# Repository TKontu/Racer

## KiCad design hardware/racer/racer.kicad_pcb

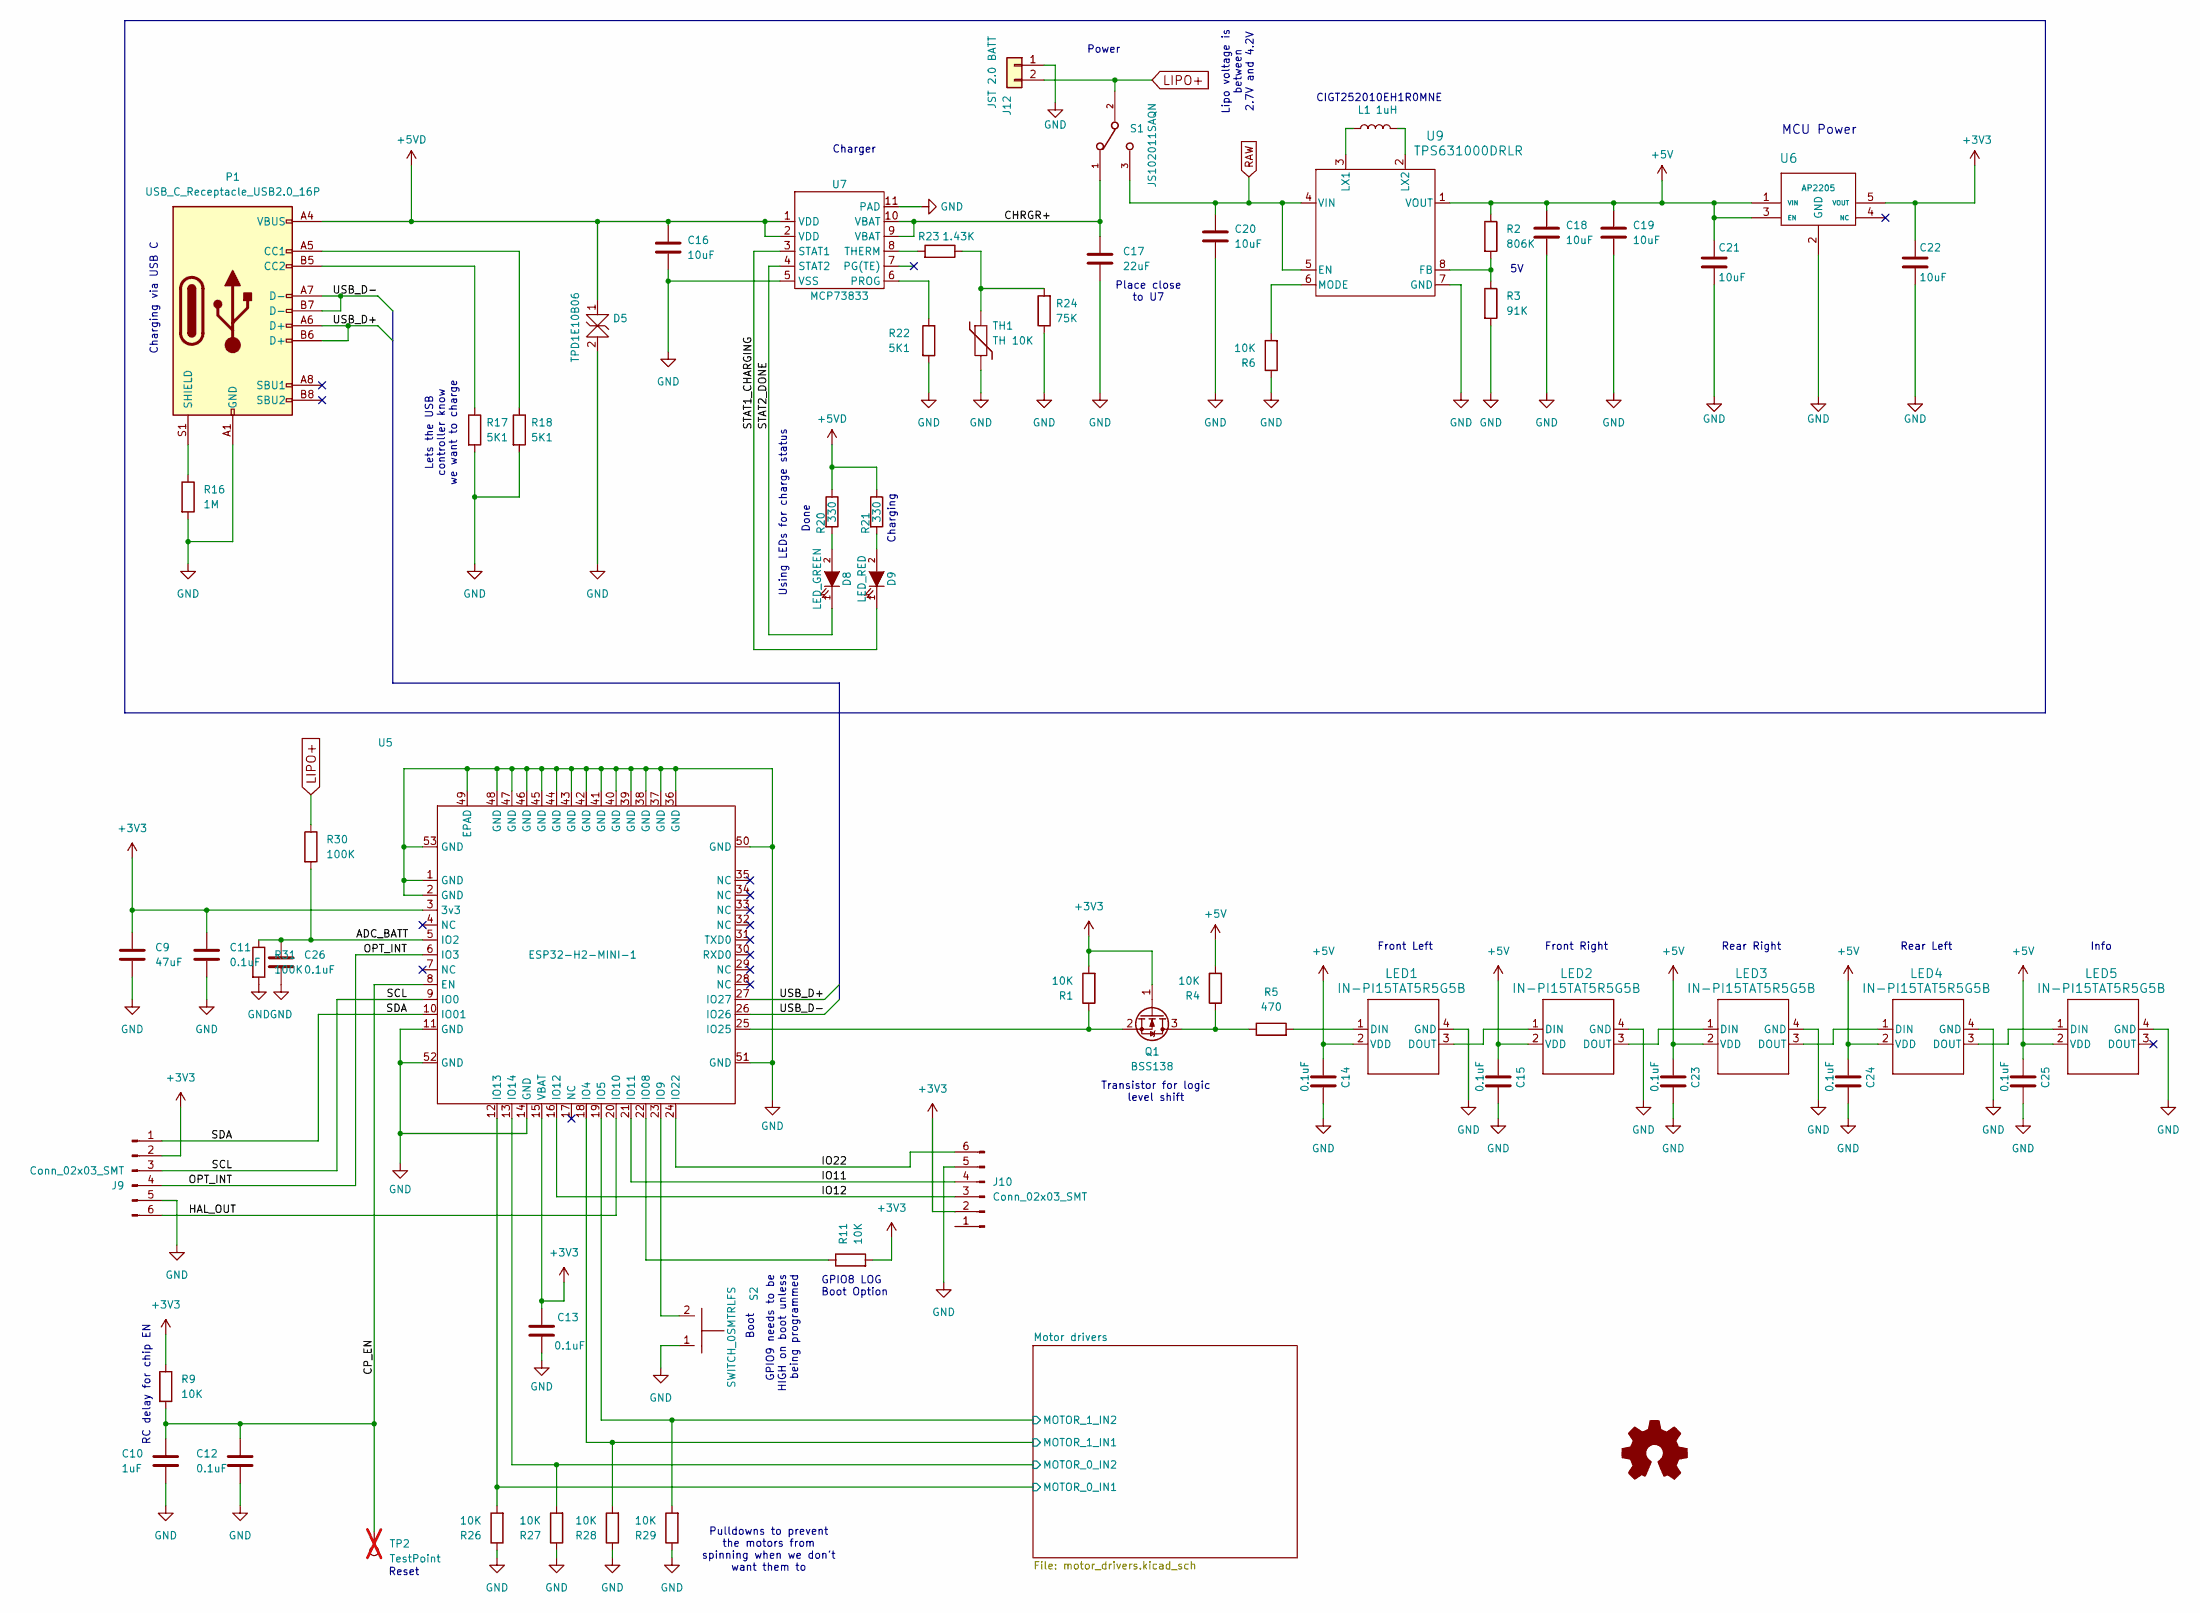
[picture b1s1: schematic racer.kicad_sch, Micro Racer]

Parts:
C9: 47uF; C_0603_1608Metric; MPN GRM188R60J476ME15D; LCSC C140782
C10: 1uF; C_0603_1608Metric; MPN CC0603KRX5R8BB105; LCSC C14664
C11, C12, C13, C14, C15, C23, C24, C25, C26: 0.1uF; C_0603_1608Metric; MPN CC0603KRX7R7BB104; LCSC C108079
C16, C18, C19, C20, C21, C22: 10uF; C_0603_1608Metric; MPN GRM188R61A106ME69D; LCSC C90053
C17: 22uF; C_0603_1608Metric; MPN GRM188R60J226MEA0J; LCSC C426040
D5: TPD1E10B06; D_SOD-523; MPN TPD1E10B06DYAR; LCSC C3712135
D8: LED_GREEN; C_0603_1608Metric; MPN 19-217/GHC-YR1S2/3T; LCSC C72043
D9: LED_RED; C_0603_1608Metric; MPN KT-0603R; LCSC C2286
J9, J10: Conn_02x03_SMT; PinHeader_2x03_P1.27mm_Vertical_SMD; MPN GRPB032VWQS-RC; LCSC C5646308
J12: JST 2.0 BATT; JST_PH_B2B-PH-K_1x02_P2.00mm_Vertical; MPN B2B-PH-K-S(LF)(SN); LCSC C131337
L1: 1uH; RES_CIGT252010; MPN CIGT252010LM1R0MNE; LCSC C307632
LED1, LED2, LED3, LED4, LED5: IN-PI15TAT5R5G5B; IN-PI15_INL; MPN IN-PI15TAT5R5G5B; LCSC C7429437
P1: USB_C_Receptacle_USB2.0_16P; GCT_USB4105-GF-A; MPN USB4105-GF-A; LCSC C3020560
Q1: BSS138; SOT-23; MPN BSS138; LCSC C52895
R1, R4, R6, R9, R11, R26, R27, R28, R29: 10K; R_0603_1608Metric; MPN WR06X103JTL; LCSC C384294
R2: 806K; R_0603_1608Metric; MPN RC0603FR-07806KL; LCSC C185311
R3: 91K; R_0603_1608Metric; MPN AR0603FR-0791KL; LCSC C855484
R5: 470; R_0603_1608Metric; MPN 0603WAF4700T5E; LCSC C23179
R16: 1M; R_0603_1608Metric; MPN RMCF0603FT1M00; LCSC C237111
R17, R18, R22: 5K1; R_0603_1608Metric; MPN RC0603FR-075K1L; LCSC C105580
R20, R21: 330; R_0603_1608Metric; MPN RC0603JR-07330RL; LCSC C105879
R23: 1.43K; R_0603_1608Metric; MPN RT0603BRE071K43L; LCSC C861730
R24: 75K; R_0603_1608Metric; MPN ERJ-PB3B7502V; LCSC C413688
R30, R31: 100K; R_0603_1608Metric; MPN WR06X1003FTL; LCSC C132374
S1: JS102011SAQN; SW_JS102011SAQN; MPN JS102011SAQN; LCSC C221660
S2: SWITCH_0SMTRLFS; MPN RKB2SJK250SMTRLFS; LCSC C2927789
TH1: TH 10K; R_0603_1608Metric; MPN NTCG163JF103HT1; LCSC C531304
TP2: TestPoint; TestPoint_Pad_1.5x1.5mm; not fitted
U5: ESP32-H2-MINI-1; MODULE_ESP32-H2-MINI-1-H2; MPN ESP32-H2-MINI-1-N4; LCSC C18203134
U6: AP2205; AP2204; MPN AP2205-33W5-7; LCSC C3750488
U7: MCP73833; SON50P300X300X100-11N; MPN MCP73833T-AMI/MF; LCSC C340160
U9: TPS631000DRLR; TPS631000DRLR_TEX; MPN TPS631000DRLR; LCSC C5219190

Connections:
+3V3: C9.1, C11.1, C13.1, C22.1, J9.2, J10.2, Q1.1 (G), R1.2, R9.1, R11.2, U5.3 (3v3), U5.15 (VBAT), U6.5 (VOUT)
+5V: C14.1, C15.1, C18.1, C19.1, C21.1, C23.1, C24.1, C25.1, LED1.2 (VDD), LED2.2 (VDD), LED3.2 (VDD), LED4.2 (VDD), LED5.2 (VDD), R2.1, R4.2, U6.1 (VIN), U6.3 (EN), U9.1 (VOUT)
+5VD: C16.1, D5.1, P1.A4 (VBUS), P1.A9 (VBUS), P1.B4 (VBUS), P1.B9 (VBUS), R20.1, R21.1, U7.1 (VDD), U7.2 (VDD)
/ADC_BATT: C26.1, R30.2, R31.1, U5.5 (IO2)
/CHRGR+: C17.1, S1.1, U7.9 (VBAT), U7.10 (VBAT)
/CP_EN: C10.1, C12.1, R9.2, TP2.1, U5.8 (EN)
/HAL_OUT: J9.6, U5.20 (IO10)
/IO11: J10.4, U5.21 (IO11)
/IO12: J10.3, U5.16 (IO12)
/IO22: J10.6, U5.24 (IO22)
/OPT_INT: J9.4, U5.6 (IO3)
/SCL: J9.3, U5.9 (IO0)
/SDA: J9.1, U5.10 (IO01)
/STAT1_CHARGING: D9.1 (K), U7.3 (STAT1)
/STAT2_DONE: D8.1 (K), U7.4 (STAT2)
/USB_D+: P1.A6 (D+), P1.B6 (D+), U5.27 (IO27)
/USB_D-: P1.A7 (D-), P1.B7 (D-), U5.26 (IO26)
GND: C9.2, C10.2, C11.2, C12.2, C13.2, C14.2, C15.2, C16.2, C17.2, C18.2, C19.2, C20.2, C21.2, C22.2, C23.2, C24.2, C25.2, C26.2, D5.2, J9.5, J10.5, J12.1, LED1.4 (GND), LED2.4 (GND), LED3.4 (GND), LED4.4 (GND), LED5.4 (GND), P1.A1 (GND), P1.A12 (GND), P1.B1 (GND), P1.B12 (GND), R3.2, R6.1, R16.2, R17.2, R18.2, R22.2, R24.1, R26.1, R27.1, R28.1, R29.1, R31.2, S2.1, TH1.2, U5.1 (GND), U5.2 (GND), U5.11 (GND), U5.14 (GND), U5.36 (GND), U5.37 (GND), U5.38 (GND), U5.39 (GND), U5.40 (GND), U5.41 (GND), U5.42 (GND), U5.43 (GND), U5.44 (GND), U5.45 (GND), U5.46 (GND), U5.47 (GND), U5.48 (GND), U5.49 (EPAD), U5.50 (GND), U5.51 (GND), U5.52 (GND), U5.53 (GND), U6.2 (GND), U7.5 (VSS), U7.11 (PAD), U9.7 (GND); also elsewhere on the board
LIPO+: J12.2, R30.1, S1.2
MOTOR_0_IN1: R26.2, U5.12 (IO13); also elsewhere on the board
MOTOR_0_IN2: R27.2, U5.13 (IO14); also elsewhere on the board
MOTOR_1_IN1: R28.2, U5.18 (IO4); also elsewhere on the board
MOTOR_1_IN2: R29.2, U5.19 (IO5); also elsewhere on the board
unnamed: D8.2 (A), R20.2
unnamed: D9.2 (A), R21.2
unnamed: LED1.1 (DIN), R5.2
unnamed: LED1.3 (DOUT), LED2.1 (DIN)
unnamed: LED2.3 (DOUT), LED3.1 (DIN)
unnamed: LED3.3 (DOUT), LED4.1 (DIN)
unnamed: LED4.3 (DOUT), LED5.1 (DIN)
unnamed: P1.A5 (CC1), R18.1
unnamed: P1.B5 (CC2), R17.1
unnamed: P1.S1 (SHIELD), R16.1
unnamed: Q1.3 (D), R4.1, R5.1
unnamed: Q1.2 (S), R1.1, U5.25 (IO25)
unnamed: R23.1, R24.2, TH1.1
unnamed: R11.1, U5.22 (IO08)
unnamed: S2.2, U5.23 (IO9)
unnamed: R22.1, U7.6 (PROG)
unnamed: R23.2, U7.8 (THERM)
unnamed: R2.2, R3.1, U9.8 (FB)
unnamed: L1.1, U9.3 (LX1)
unnamed: L1.2, U9.2 (LX2)
unnamed: R6.2, U9.6 (MODE)
RAW: C20.1, S1.3, U9.4 (VIN), U9.5 (EN); also elsewhere on the board

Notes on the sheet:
Lipo voltage is between 2.7V and 4.2V
Charging via USB C
Using LEDs for charge status
RC delay for chip EN
Lets the USB controller know we want to charge
Front Right
Power
Rear Right
Reset
GPIO9 needs to be HIGH on boot unless being programmed
Pulldowns to prevent the motors from spinning when we don't want them to
Charger
GPIO8 LOG Boot Option
Charging
Done
Info
MCU Power
Front Left
CIGT252010EH1R0MNE
Rear Left
Place close to U7
Boot
Transistor for logic level shift

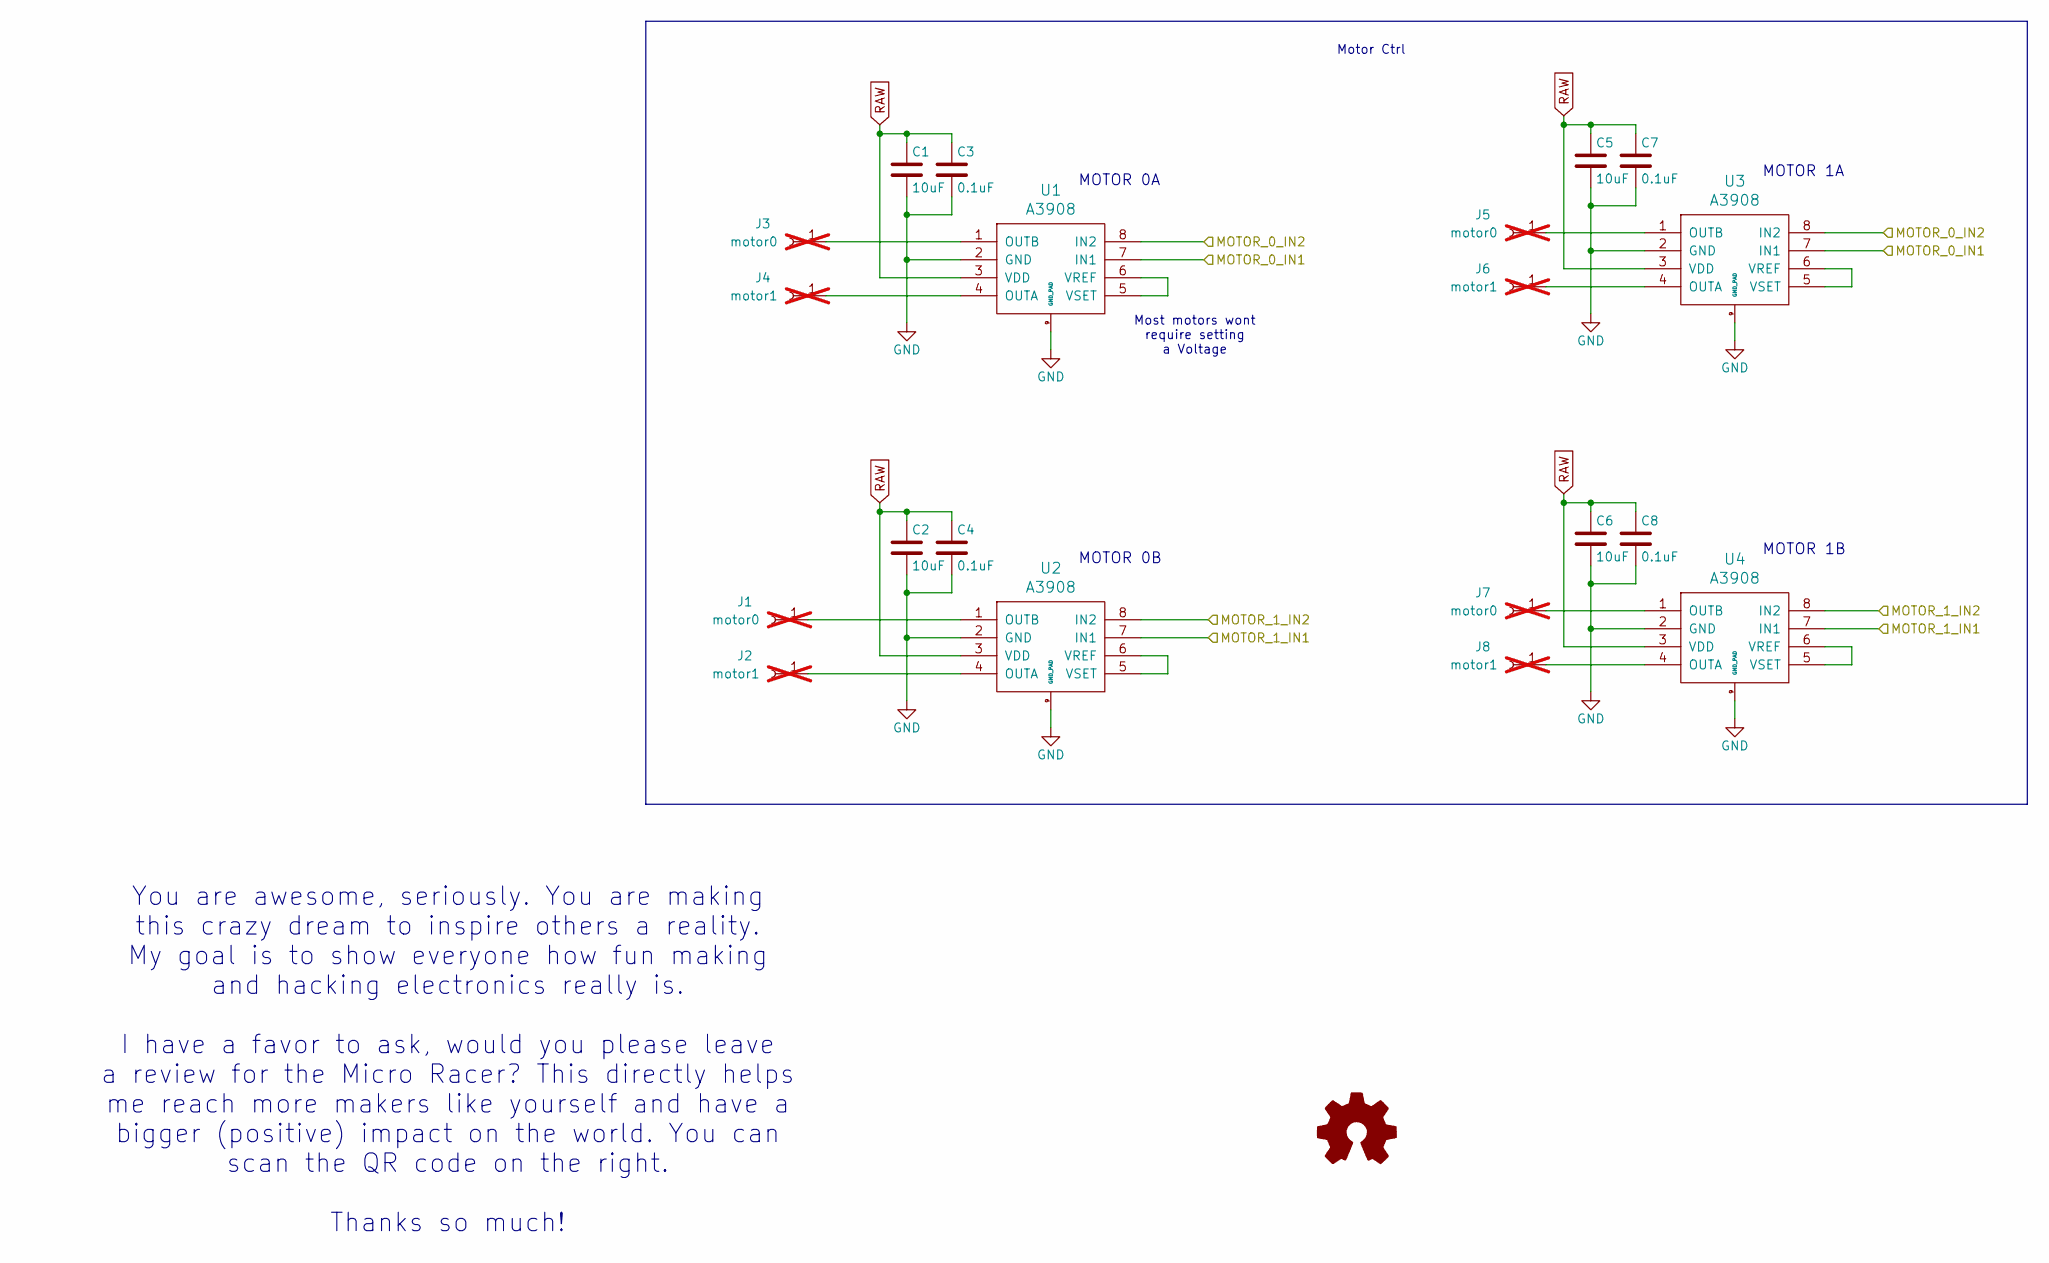
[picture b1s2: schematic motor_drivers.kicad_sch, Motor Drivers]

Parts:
C1, C2, C5, C6: 10uF; C_0603_1608Metric; MPN GRM188R61A106ME69D; LCSC C90053
C3, C4, C7, C8: 0.1uF; C_0603_1608Metric; MPN CC0603KRX7R7BB104; LCSC C108079
J1, J3, J5, J7: motor0; TestPoint_Pad_2.0x2.0mm; not fitted
J2, J4, J6, J8: motor1; TestPoint_Pad_2.0x2.0mm; not fitted
U1, U2, U3, U4: A3908; MPN A3908EEETR-T; LCSC C459250

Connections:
GND: C1.2, C2.2, C3.2, C4.2, C5.2, C6.2, C7.2, C8.2, U1.2 (GND), U1.9 (GND_PAD), U2.2 (GND), U2.9 (GND_PAD), U3.2 (GND), U3.9 (GND_PAD), U4.2 (GND), U4.9 (GND_PAD); also elsewhere on the board
MOTOR_0_IN1: U1.7 (IN1), U3.7 (IN1); also elsewhere on the board
MOTOR_0_IN2: U1.8 (IN2), U3.8 (IN2); also elsewhere on the board
MOTOR_1_IN1: U2.7 (IN1), U4.7 (IN1); also elsewhere on the board
MOTOR_1_IN2: U2.8 (IN2), U4.8 (IN2); also elsewhere on the board
unnamed: J1.1, U2.1 (OUTB)
unnamed: J2.1, U2.4 (OUTA)
unnamed: J3.1, U1.1 (OUTB)
unnamed: J4.1, U1.4 (OUTA)
unnamed: J5.1, U3.1 (OUTB)
unnamed: J6.1, U3.4 (OUTA)
unnamed: J7.1, U4.1 (OUTB)
unnamed: J8.1, U4.4 (OUTA)
unnamed: U1.5 (VSET), U1.6 (VREF)
unnamed: U2.5 (VSET), U2.6 (VREF)
unnamed: U3.5 (VSET), U3.6 (VREF)
unnamed: U4.5 (VSET), U4.6 (VREF)
RAW: C1.1, C2.1, C3.1, C4.1, C5.1, C6.1, C7.1, C8.1, U1.3 (VDD), U2.3 (VDD), U3.3 (VDD), U4.3 (VDD); also elsewhere on the board

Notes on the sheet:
Most motors wont require setting a Voltage
You are awesome, seriously. You are making this crazy dream to inspire others a reality. My goal is to show everyone how fun making and hacking electronics really is. I have a favor to ask, would you please leave a review for the Micro Racer? This directly helps me reach more makers like yourself a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
MOTOR 1B
MOTOR 0A
Motor Ctrl
MOTOR 1A
MOTOR 0B

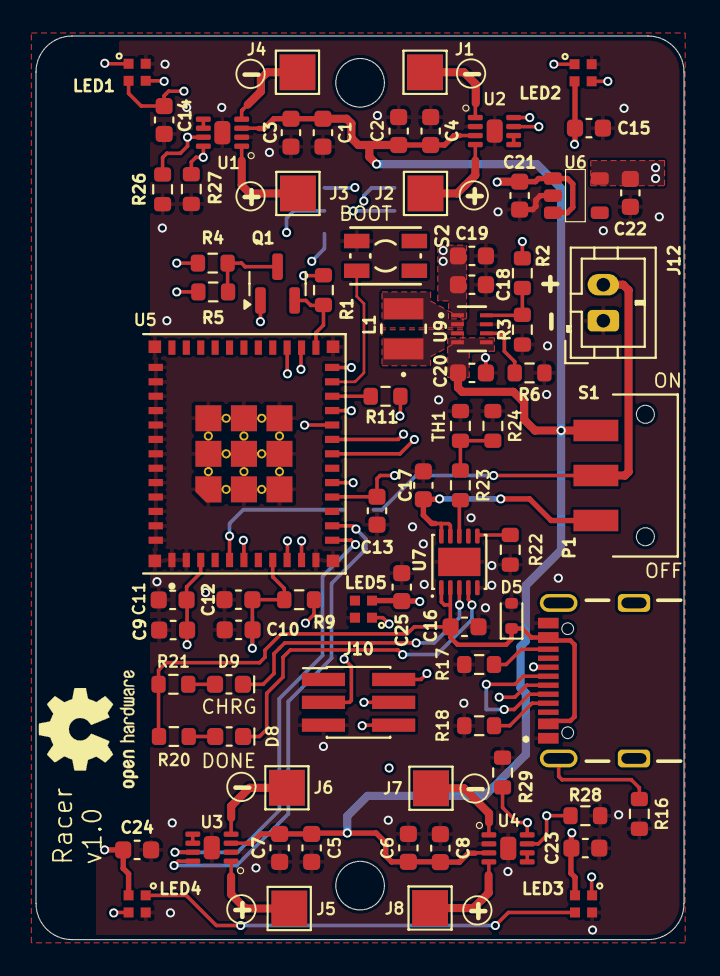
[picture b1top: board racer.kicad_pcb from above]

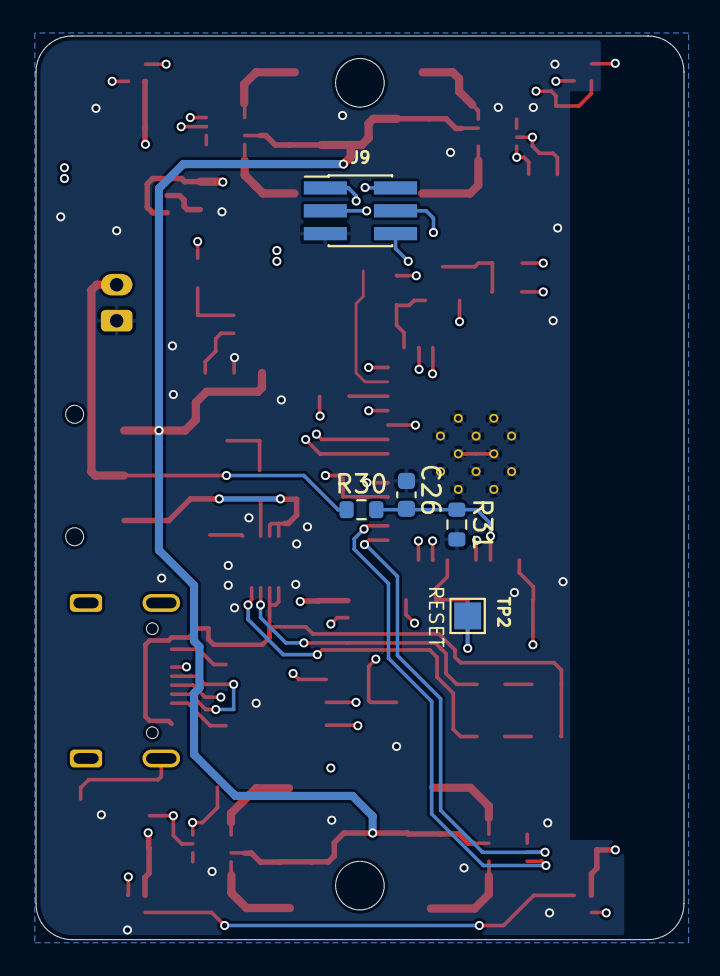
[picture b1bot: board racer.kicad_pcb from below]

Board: 4 copper layers, 36.0 x 50.2 mm, 82 parts (5 on the bottom side), 57 nets.

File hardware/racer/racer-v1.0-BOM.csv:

Designator,Quantity,Manufacturer Part Number,Package/Footprint,Description
U9,1,TPS631000DRLR,TPS631000DRLR_TEX,TPS631000DRLR
"R6,R26,R28,R29,R9,R1,R27,R11,R4",9,WR06X103 JTL,R_0603_1608Metric,10K
"C2,C16,C20,C18,C5,C6,C19,C1,C22,C21",10,GRM188R61A106ME69D,C_0603_1608Metric,10uF
S2,1,RKB2SJK250SMTR LFS,SWITCH_0SMTRLFS,SWITCH_0SMTRLFS
"C7,C12,C13,C24,C15,C3,C8,C14,C4,C23,C11,C25,C26",13,CC0603KRX7R7BB104,C_0603_1608Metric,0.1uF
R2,1,RC0603FR-07806KL,R_0603_1608Metric,806K
U6,1,AP2205-33W5-7,AP2204,AP2205
R23,1,RT0603BRE071K43L,R_0603_1608Metric,1.43K
"J9,J10",2,GRPB032VWQS-RC,PinHeader_2x03_P1.27mm_Vertical_SMD,Conn_02x03_SMT
Q1,1,BSS138,SOT-23,BSS138
D9,1,150060RS75000,C_0603_1608Metric,LED_RED
"R17,R22,R18",3,RC0603FR-075K1L,R_0603_1608Metric,5K1
"LED1,LED3,LED5,LED4,LED2",5,IN-PI15TAT5R5G5B,IN-PI15_INL,IN-PI15TAT5R5G5B
D8,1,150060GS75000,C_0603_1608Metric,LED_GREEN
"U4,U1,U2,U3",4,A3908EEETR-T,A3908,A3908
J12,1,B2B-PH-K-S,JST_PH_B2B-PH-K_1x02_P2.00mm_Vertical,JST 2.0 BATT
P1,1,USB4105-GF-A,GCT_USB4105-GF-A,USB_C_Receptacle_USB2.0_16P
TH1,1,NTCG163JF103HT1,R_0603_1608Metric,TH 10K
U5,1,ESP32-H2-MINI-1,MODULE_ESP32-H2-MINI-1-H2,ESP32-H2-MINI-1
R3,1,AR0603FR-0791KL,R_0603_1608Metric,91K
R5,1,ESR03EZPF4700,R_0603_1608Metric,470
L1,1,CIGT252010EH1R0MNE,RES_CIGT252010,1uH
C10,1,CC0603KRX5R8BB105,C_0603_1608Metric,1uF
"R21,R20",2,RC0603JR-07330RL,R_0603_1608Metric,330
D5,1,TPD1E10B06DYAR,D_SOD-523,TPD1E10B06
S1,1,JS102011SAQN,SW_JS102011SAQN,JS102011SAQN
R24,1,ERJ-PB3B7502V,R_0603_1608Metric,75K
U7,1,MCP73833T-AMI/MF,SON50P300X300X100-11N,MCP73833
C17,1,GRM188R60J226MEA0J,C_0603_1608Metric,22uF
R16,1,RMCF0603FT1M00,R_0603_1608Metric,1M
C9,1,GRM188R60J476ME15D,C_0603_1608Metric,47uF
"R30,R31",2,WR06X1003FTL,R_0603_1608Metric,100K

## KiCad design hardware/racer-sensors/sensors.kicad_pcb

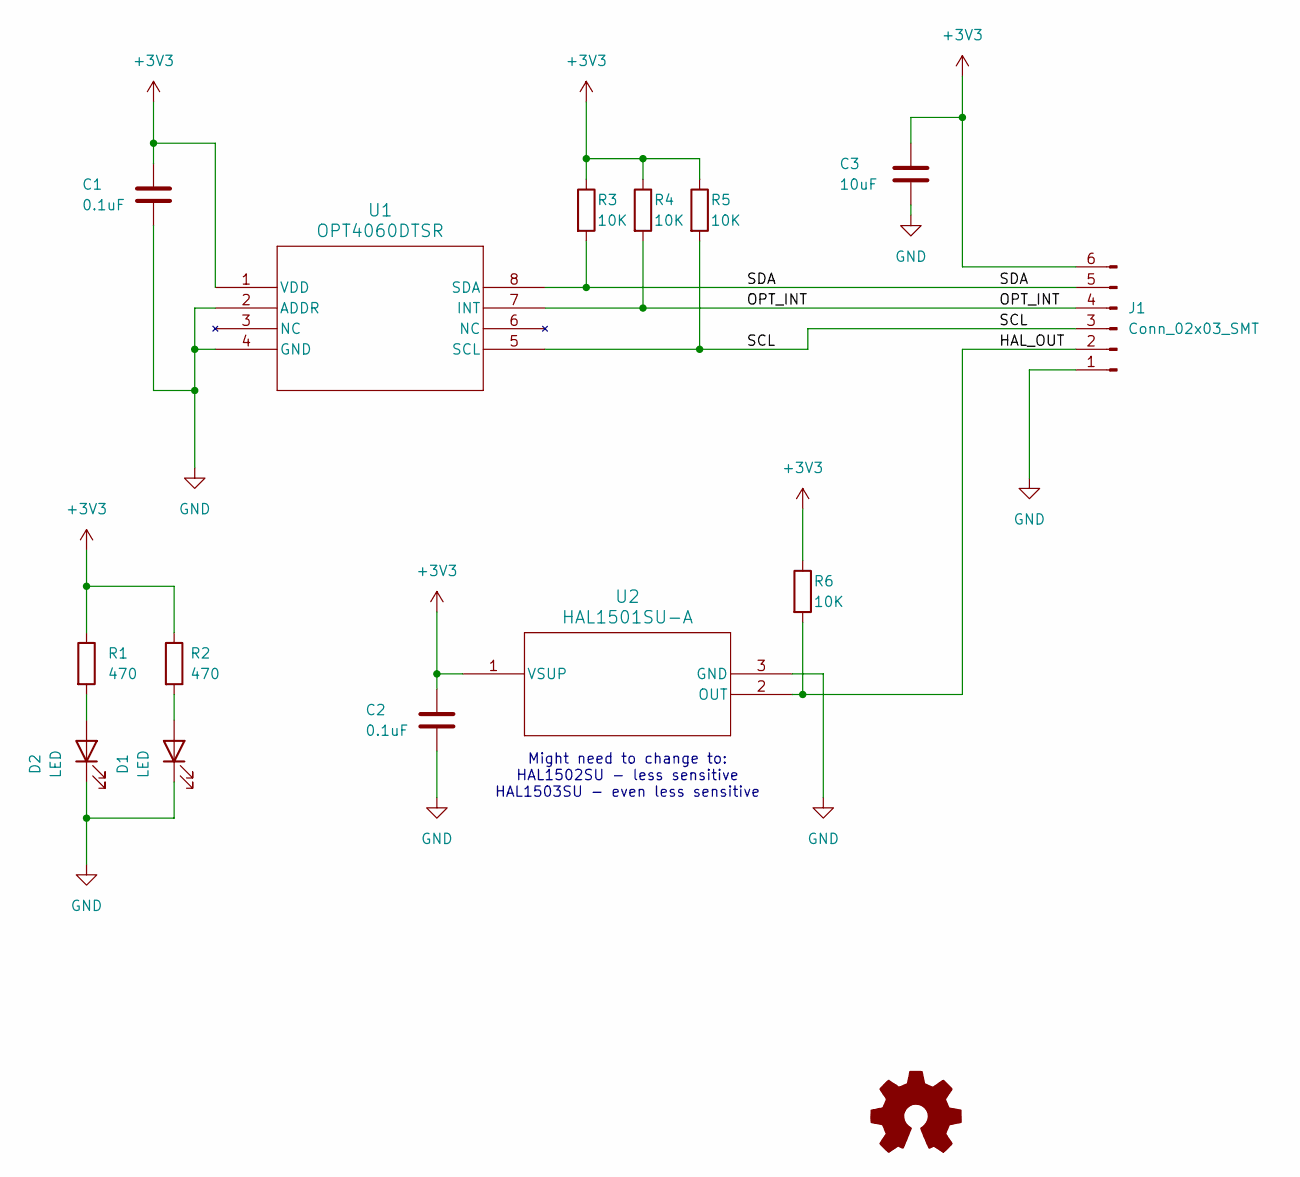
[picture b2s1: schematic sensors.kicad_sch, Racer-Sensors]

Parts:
C1, C2: 0.1uF; C_0603_1608Metric; MPN CC0603KRX7R7BB104; LCSC C108079
C3: 10uF; C_0603_1608Metric; MPN GRM188R61A106ME69D; LCSC C90053
D1, D2: LED; LED_0603_1608Metric; MPN IN-S63AT5UW; LCSC C7207730
J1: Conn_02x03_SMT; PinHeader_2x03_P1.27mm_Vertical_SMD; MPN 20021321-00006C4LF; LCSC C2931358
R1, R2: 470; R_0603_1608Metric; MPN 0603WAF4700T5E; LCSC C23179
R3, R4, R5, R6: 10K; R_0603_1608Metric; MPN WR06X103JTL; LCSC C384294
U1: OPT4060DTSR; FCSOT8_DTS_TEX; MPN OPT4060DTSR; LCSC C31267548
U2: HAL1501SU-A; SOT-23_TO-236_TDK; MPN HAL1501SU-A; LCSC C2152449

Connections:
+3V3: C1.1, C2.1, C3.1, J1.6, R1.1, R2.1, R3.1, R4.1, R5.1, R6.1, U1.1 (VDD), U2.1 (VSUP)
/HAL_OUT: J1.2, R6.2, U2.2 (OUT)
/OPT_INT: J1.4, R4.2, U1.7 (INT)
/SCL: J1.3, R5.2, U1.5 (SCL)
/SDA: J1.5, R3.2, U1.8 (SDA)
GND: C1.2, C2.2, C3.2, D1.1 (K), D2.1 (K), J1.1, U1.2 (ADDR), U1.4 (GND), U2.3 (GND)
unnamed: D1.2 (A), R2.2
unnamed: D2.2 (A), R1.2

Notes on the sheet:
Might need to change to: HAL1502SU - less sensitive HAL1503SU - even less sensitive

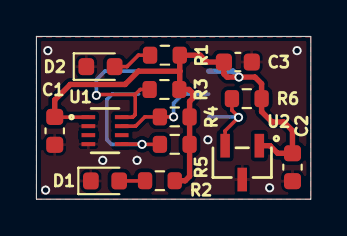
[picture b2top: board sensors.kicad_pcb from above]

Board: 4 copper layers, 15.2 x 9.0 mm, 14 parts (1 on the bottom side), 8 nets.

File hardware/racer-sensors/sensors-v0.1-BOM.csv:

Id,Designator,Footprint,Quantity,Designation,Supplier and ref,Notes
1,"R4,R5,R6,R3",R_0603_1608Metric,4,10K,WR06X103 JTL,
2,"D1,D2",LED_0603_1608Metric,2,LED,IN-S63AT5UW,
3,"R2,R1",R_0603_1608Metric,2,R,ESR03EZPF4700,"Note: I used a 470ohm resistor, but this might need to be adjusted to vary brightness "
4,C3,C_0603_1608Metric,1,10uF,GRM188R61A106ME69D,
5,"C1,C2",C_0603_1608Metric,2,0.1uF,CC0603KRX7R7BB104,
6,U2,SOT-23_TO-236_TDK,1,HAL1501SU-A,HAL1501SU-A,
7,U1,FCSOT8_DTS_TEX,1,OPT4060DTSR,OPT4060DTSR,
8,J1,PinHeader_2x03_P1.27mm_Vertical_SMD,1,Conn_02x03_SMT,20021321-00006C4LF,
